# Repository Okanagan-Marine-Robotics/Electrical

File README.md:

# Electrical
Repo For Electrical pcbs and documentation

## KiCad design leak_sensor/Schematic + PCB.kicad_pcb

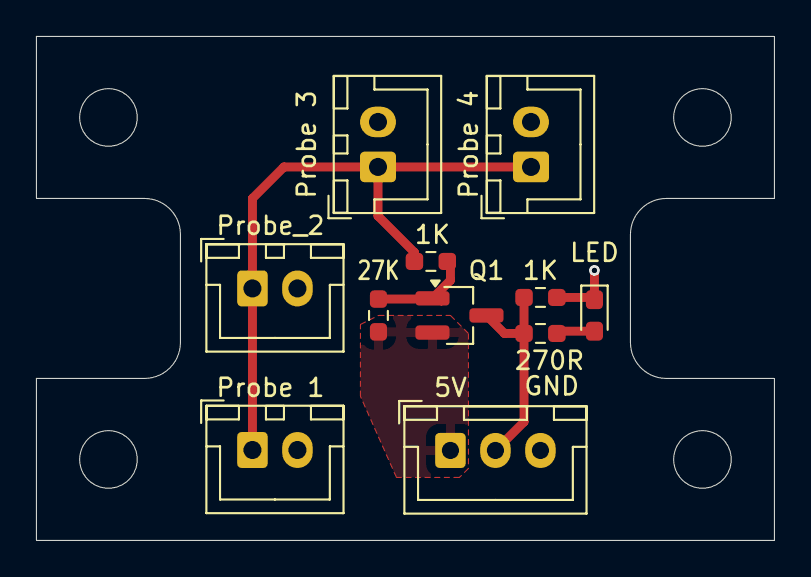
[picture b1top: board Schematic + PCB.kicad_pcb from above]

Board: 2 copper layers, 41.0 x 28.0 mm, 11 parts (0 on the bottom side), 6 nets.

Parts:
J1: 5V; JST_XH_B3B-XH-A_1x03_P2.50mm_Vertical
J2: Probe 3; JST_XH_B2B-XH-A_1x02_P2.50mm_Vertical
J3: Probe 1; JST_XH_B2B-XH-A_1x02_P2.50mm_Vertical
J4: Probe 4; JST_XH_B2B-XH-A_1x02_P2.50mm_Vertical
J5: Probe_2; JST_XH_B2B-XH-A_1x02_P2.50mm_Vertical
LED1: LED; LED_0603_1608Metric_Pad1.05x0.95mm_HandSolder
Q1: BC859W; SOT-23_Handsoldering
R1: 270R; R_0603_1608Metric_Pad0.98x0.95mm_HandSolder
R2, R4: 1K; R_0603_1608Metric_Pad0.98x0.95mm_HandSolder
R3: 27K; R_0603_1608Metric_Pad0.98x0.95mm_HandSolder

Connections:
+5V: J1.1, Q1.2 (E), R3.1
GND: J1.3, J2.2, J3.2, J4.2, J5.2, LED1.1 (K), R2.2
unnamed: J1.2, Q1.3 (C), R1.1, R2.1
unnamed: J2.1, J3.1, J4.1, J5.1, R4.2
unnamed: LED1.2 (A), R1.2
unnamed: Q1.1 (B), R3.2, R4.1

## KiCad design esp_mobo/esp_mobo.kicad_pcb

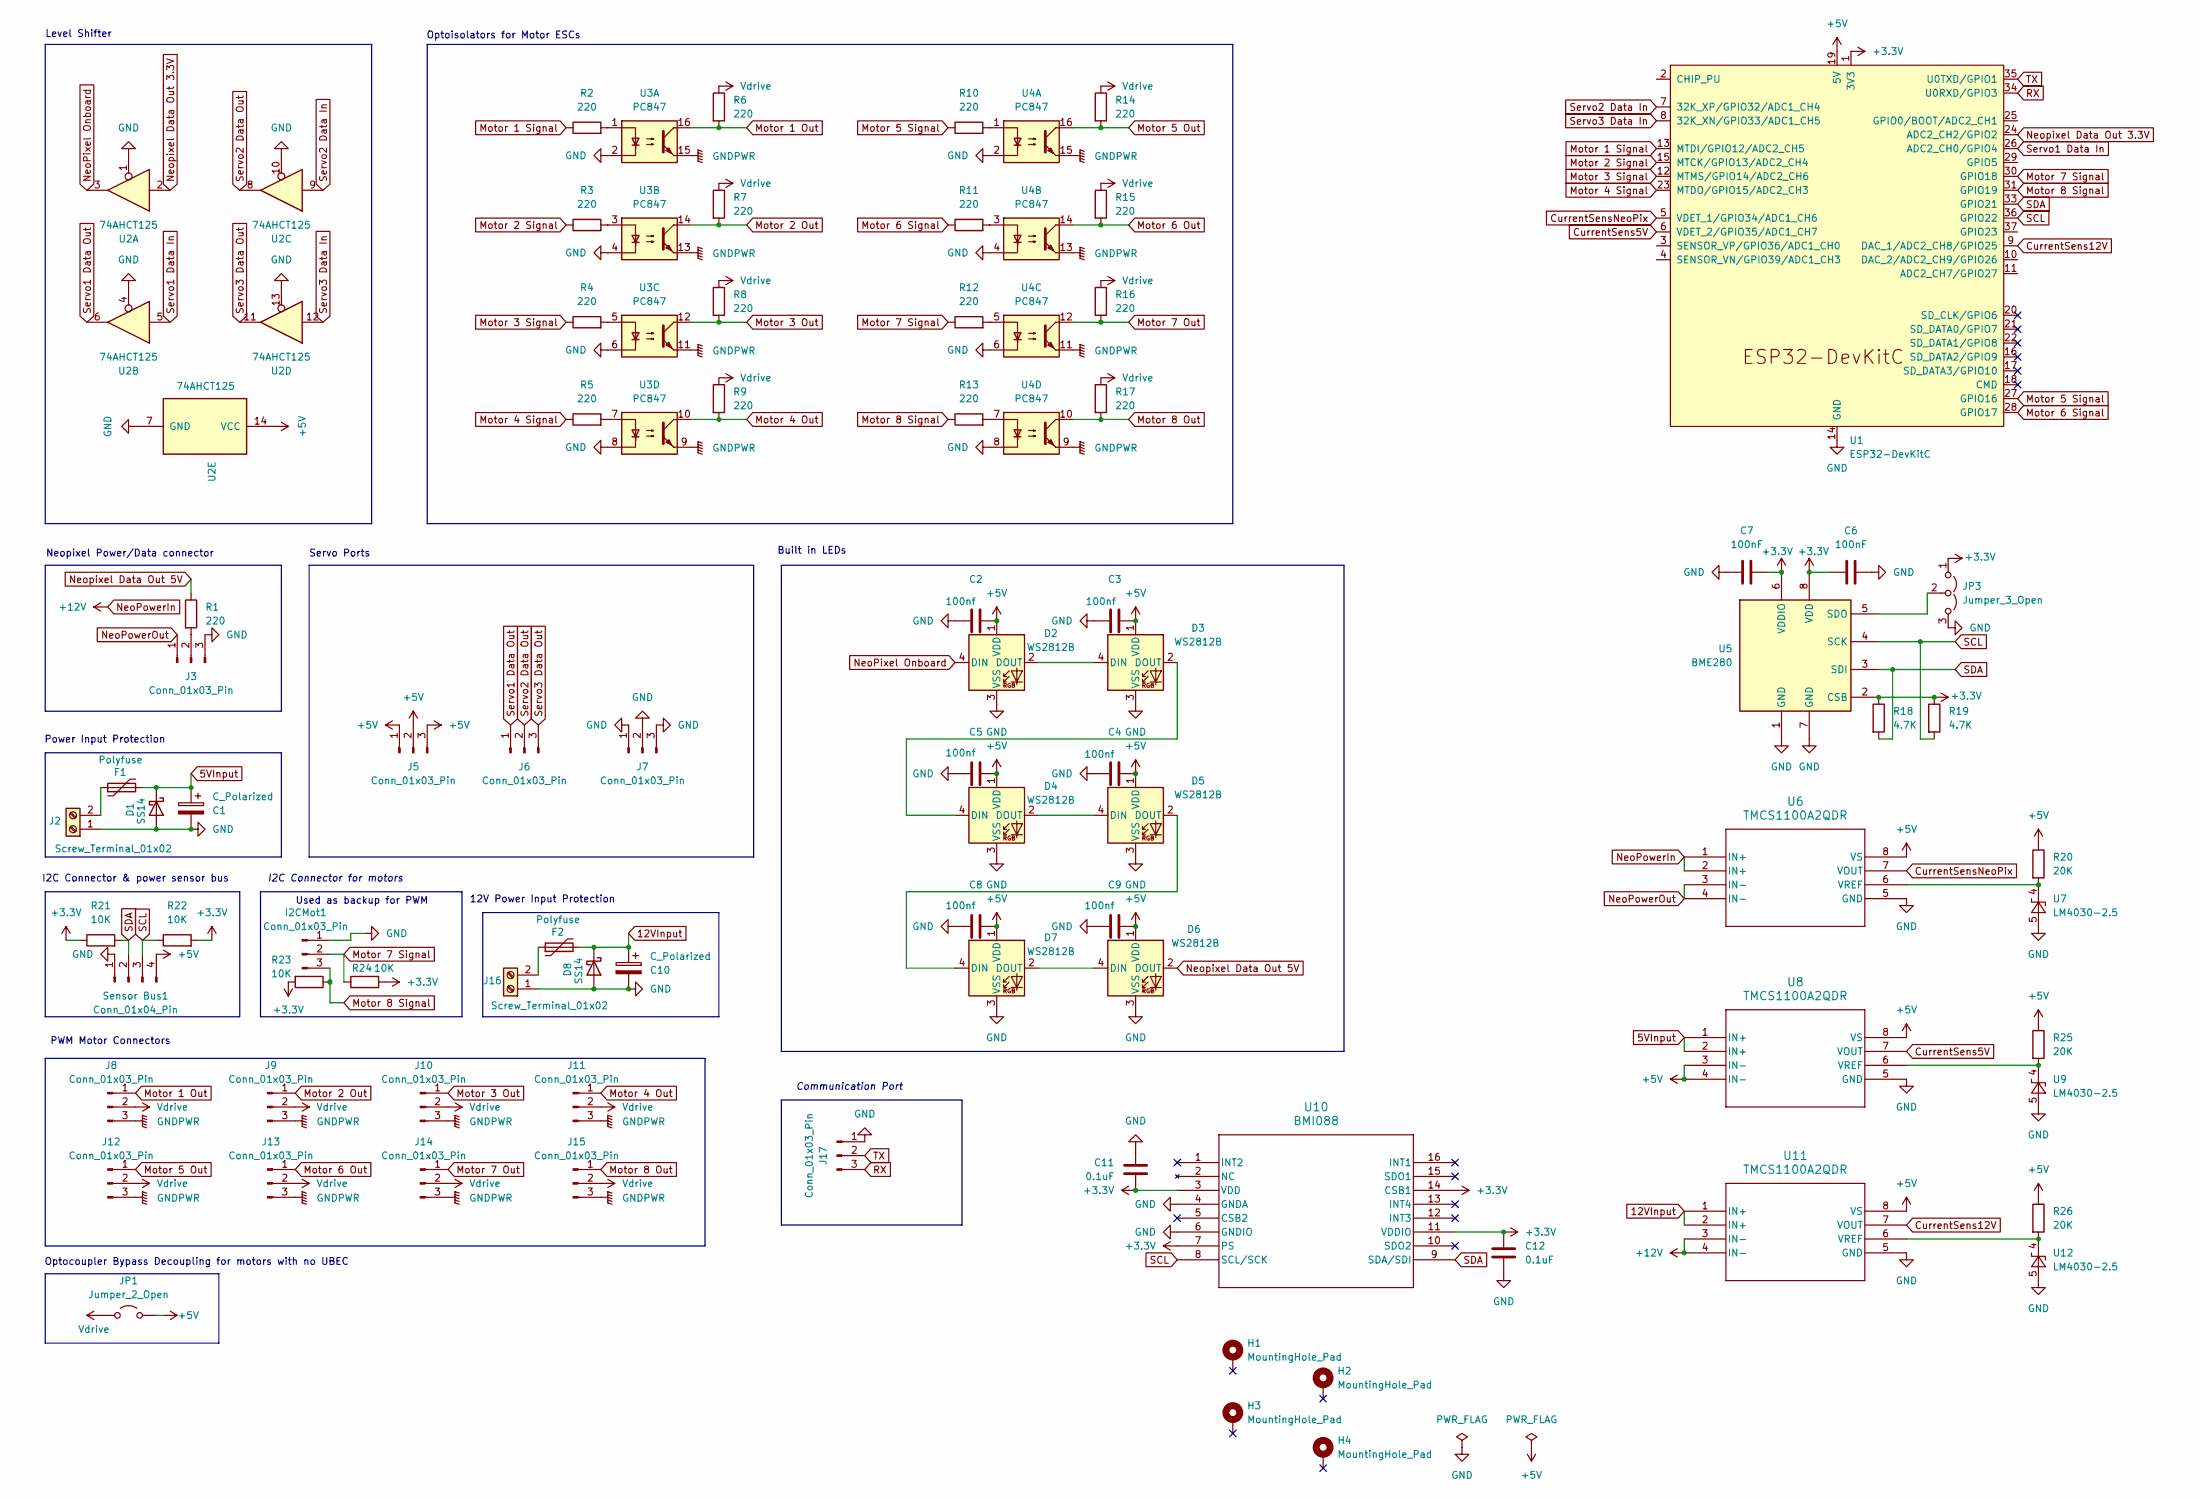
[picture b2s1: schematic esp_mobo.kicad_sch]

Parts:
C1, C10: C_Polarized; CP_Radial_D5.0mm_P2.00mm
C2, C3, C4, C5, C8, C9: 100nf; C_0603_1608Metric
C6, C7: 100nF; C_0603_1608Metric_Pad1.08x0.95mm_HandSolder
C11, C12: 0.1uF; C_0603_1608Metric
D1, D8: SS14; D_SMA
D2, D3, D4, D5, D6, D7: WS2812B; LED_WS2812B_PLCC4_5.0x5.0mm_P3.2mm
F1, F2: Polyfuse; Fuse_Bourns_MF-RG300
H1, H2, H3, H4: MountingHole_Pad; MountingHole_3.2mm_M3_Pad
I2CMot1: Conn_01x03_Pin; JST_XH_B3B-XH-AM_1x03_P2.50mm_Vertical
J2, J16: Screw_Terminal_01x02; TerminalBlock_TE_282834-2_1x02_P2.54mm_Horizontal
J3, J17: Conn_01x03_Pin; JST_XH_B3B-XH-AM_1x03_P2.50mm_Vertical
J5, J6, J7, J8, J9, J10, J11, J12, J13, J14, J15: Conn_01x03_Pin; PinHeader_1x03_P2.54mm_Vertical_small_courtyard
JP1: Jumper_2_Open; PinHeader_1x02_P2.54mm_Vertical
JP3: Jumper_3_Open; PinHeader_1x03_P2.54mm_Vertical
R1: 220; R_0805_2012Metric_Pad1.20x1.40mm_HandSolder
R2, R3, R4, R5, R6, R7, R8, R9, R10, R11, R12, R13, R14, R15, R16, R17: 220; R_0603_1608Metric_Pad0.98x0.95mm_HandSolder
R18, R19: 4.7K; R_0603_1608Metric_Pad0.98x0.95mm_HandSolder
R20, R25, R26: 20K; R_0603_1608Metric_Pad0.98x0.95mm_HandSolder
R21, R22, R23, R24: 10K; R_0603_1608Metric_Pad0.98x0.95mm_HandSolder
Sensor Bus1: Conn_01x04_Pin; JST_XH_B4B-XH-AM_1x04_P2.50mm_Vertical
U1: ESP32-DevKitC
U2: 74AHCT125; DIP-14_W7.62mm
U3, U4: PC847; DIP-16_W7.62mm
U5: BME280; Bosch_LGA-8_2.5x2.5mm_P0.65mm_ClockwisePinNumbering
U6, U8, U11: TMCS1100A2QDR; SOIC8_D_TEX
U7, U9, U12: LM4030-2.5; SOT-23-5
U10: BMI088; QFN_BMI085_BOS

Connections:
5VInput: C1.1, D1.1 (K), F1.2, U8.1 (IN+), U8.2 (IN+)
12VInput: C10.1, D8.1 (K), F2.2, U11.1 (IN+), U11.2 (IN+)
+3.3V: C6.1, C7.2, C11.1, C12.1, JP3.1 (A), R18.1, R19.1, R21.1, R22.2, R23.2, R24.2, U1.1 (3V3), U5.2 (CSB), U5.6 (VDDIO), U5.8 (VDD), U10.3 (VDD), U10.7 (PS), U10.11 (VDDIO), U10.14 (CSB1)
+5V: C2.2, C3.2, C4.2, C5.2, C8.2, C9.2, D2.1 (VDD), D3.1 (VDD), D4.1 (VDD), D5.1 (VDD), D6.1 (VDD), D7.1 (VDD), J5.1, J5.2, J5.3, JP1.2 (B), R20.1, R25.1, R26.1, Sensor Bus1.4, U1.19 (5V), U2.14 (VCC), U6.8 (VS), U8.3 (IN-), U8.4 (IN-), U8.8 (VS), U11.8 (VS)
CurrentSens5V: U1.6 (VDET_2/GPIO35/ADC1_CH7), U8.7 (VOUT)
CurrentSens12V: U1.9 (DAC_1/ADC2_CH8/GPIO25), U11.7 (VOUT)
CurrentSensNeoPix: U1.5 (VDET_1/GPIO34/ADC1_CH6), U6.7 (VOUT)
GND: C1.2, C2.1, C3.1, C4.1, C5.1, C6.2, C7.1, C8.1, C9.1, C10.2, C11.2, C12.2, D1.2 (A), D2.3 (VSS), D3.3 (VSS), D4.3 (VSS), D5.3 (VSS), D6.3 (VSS), D7.3 (VSS), D8.2 (A), I2CMot1.1, J2.1, J3.3, J7.1, J7.2, J7.3, J16.1, J17.1, JP3.3 (B), Sensor Bus1.1, U1.14 (GND), U1.32 (GND), U1.38 (GND), U2.1, U2.4, U2.7 (GND), U2.10, U2.13, U3.2, U3.4, U3.6, U3.8, U4.2, U4.4, U4.6, U4.8, U5.1 (GND), U5.7 (GND), U6.5 (GND), U7.5 (A), U8.5 (GND), U9.5 (A), U10.4 (GNDA), U10.6 (GNDIO), U11.5 (GND), U12.5 (A)
GNDPWR: J8.3, J9.3, J10.3, J11.3, J12.3, J13.3, J14.3, J15.3, U3.9, U3.11, U3.13, U3.15, U4.9, U4.11, U4.13, U4.15
Motor 1 Out: J8.1, R6.2, U3.16
Motor 1 Signal: R2.1, U1.13 (MTDI/GPIO12/ADC2_CH5)
Motor 2 Out: J9.1, R7.2, U3.14
Motor 2 Signal: R3.1, U1.15 (MTCK/GPIO13/ADC2_CH4)
Motor 3 Out: J10.1, R8.2, U3.12
Motor 3 Signal: R4.1, U1.12 (MTMS/GPIO14/ADC2_CH6)
Motor 4 Out: J11.1, R9.2, U3.10
Motor 4 Signal: R5.1, U1.23 (MTDO/GPIO15/ADC2_CH3)
Motor 5 Out: J12.1, R14.2, U4.16
Motor 5 Signal: R10.1, U1.27 (GPIO16)
Motor 6 Out: J13.1, R15.2, U4.14
Motor 6 Signal: R11.1, U1.28 (GPIO17)
Motor 7 Out: J14.1, R16.2, U4.12
Motor 7 Signal: I2CMot1.2, R12.1, R24.1, U1.30 (GPIO18)
Motor 8 Out: J15.1, R17.2, U4.10
Motor 8 Signal: I2CMot1.3, R13.1, R23.1, U1.31 (GPIO19)
NeoPixel Onboard: D2.4 (DIN), U2.3
NeoPowerIn: U6.1 (IN+), U6.2 (IN+), U11.3 (IN-), U11.4 (IN-)
NeoPowerOut: J3.1, U6.3 (IN-), U6.4 (IN-)
Neopixel Data Out 3.3V: U1.24 (ADC2_CH2/GPIO2), U2.2
Neopixel Data Out 5V: D6.2 (DOUT), R1.1
unnamed: D2.2 (DOUT), D3.4 (DIN)
unnamed: D3.2 (DOUT), D4.4 (DIN)
unnamed: D4.2 (DOUT), D5.4 (DIN)
unnamed: D5.2 (DOUT), D7.4 (DIN)
unnamed: D6.4 (DIN), D7.2 (DOUT)
unnamed: F1.1, J2.2
unnamed: J3.2, R1.2
unnamed: F2.1, J16.2
unnamed: JP3.2 (C), U5.5 (SDO)
unnamed: R2.2, U3.1
unnamed: R3.2, U3.3
unnamed: R4.2, U3.5
unnamed: R5.2, U3.7
unnamed: R10.2, U4.1
unnamed: R11.2, U4.3
unnamed: R12.2, U4.5
unnamed: R13.2, U4.7
unnamed: R20.2, U6.6 (VREF), U7.4 (K)
unnamed: R25.2, U8.6 (VREF), U9.4 (K)
unnamed: R26.2, U11.6 (VREF), U12.4 (K)
RX: J17.3, U1.34 (U0RXD/GPIO3)
SCL: R19.2, R22.1, Sensor Bus1.3, U1.36 (GPIO22), U5.4 (SCK), U10.8 (SCL/SCK)
SDA: R18.2, R21.2, Sensor Bus1.2, U1.33 (GPIO21), U5.3 (SDI), U10.9 (SDA/SDI)
Servo1 Data In: U1.26 (ADC2_CH0/GPIO4), U2.5
Servo1 Data Out: J6.1, U2.6
Servo2 Data In: U1.7 (32K_XP/GPIO32/ADC1_CH4), U2.9
Servo2 Data Out: J6.2, U2.8
Servo3 Data In: U1.8 (32K_XN/GPIO33/ADC1_CH5), U2.12
Servo3 Data Out: J6.3, U2.11
TX: J17.2, U1.35 (U0TXD/GPIO1)
Vdrive: J8.2, J9.2, J10.2, J11.2, J12.2, J13.2, J14.2, J15.2, JP1.1 (A), R6.1, R7.1, R8.1, R9.1, R14.1, R15.1, R16.1, R17.1

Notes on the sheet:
Communication Port
Level Shifter
Built in LEDs
12V Power Input Protection
Neopixel Power/Data connector
Servo Ports
PWM Motor Connectors
Used as backup for PWM
I2C Connector for motors
Optocoupler Bypass Decoupling for motors with no UBEC
Optoisolators for Motor ESCs
Power Input Protection
I2C Connector & power sensor bus

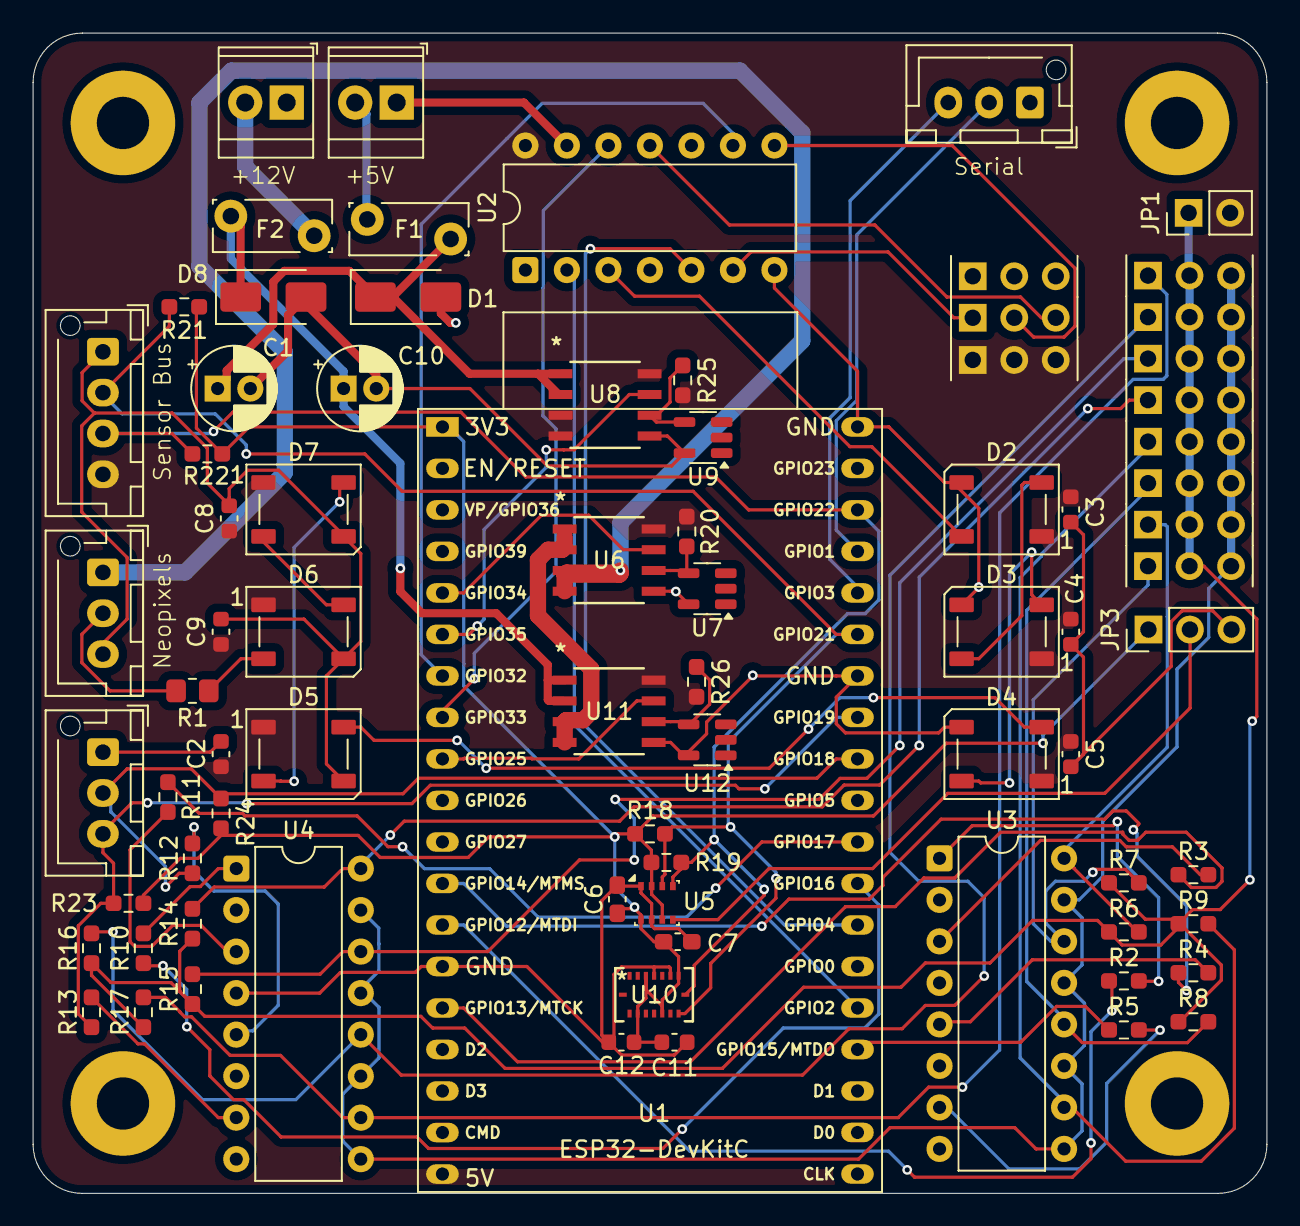
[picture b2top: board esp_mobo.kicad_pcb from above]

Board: 2 copper layers, 75.5 x 71.0 mm, 83 parts (0 on the bottom side), 61 nets.

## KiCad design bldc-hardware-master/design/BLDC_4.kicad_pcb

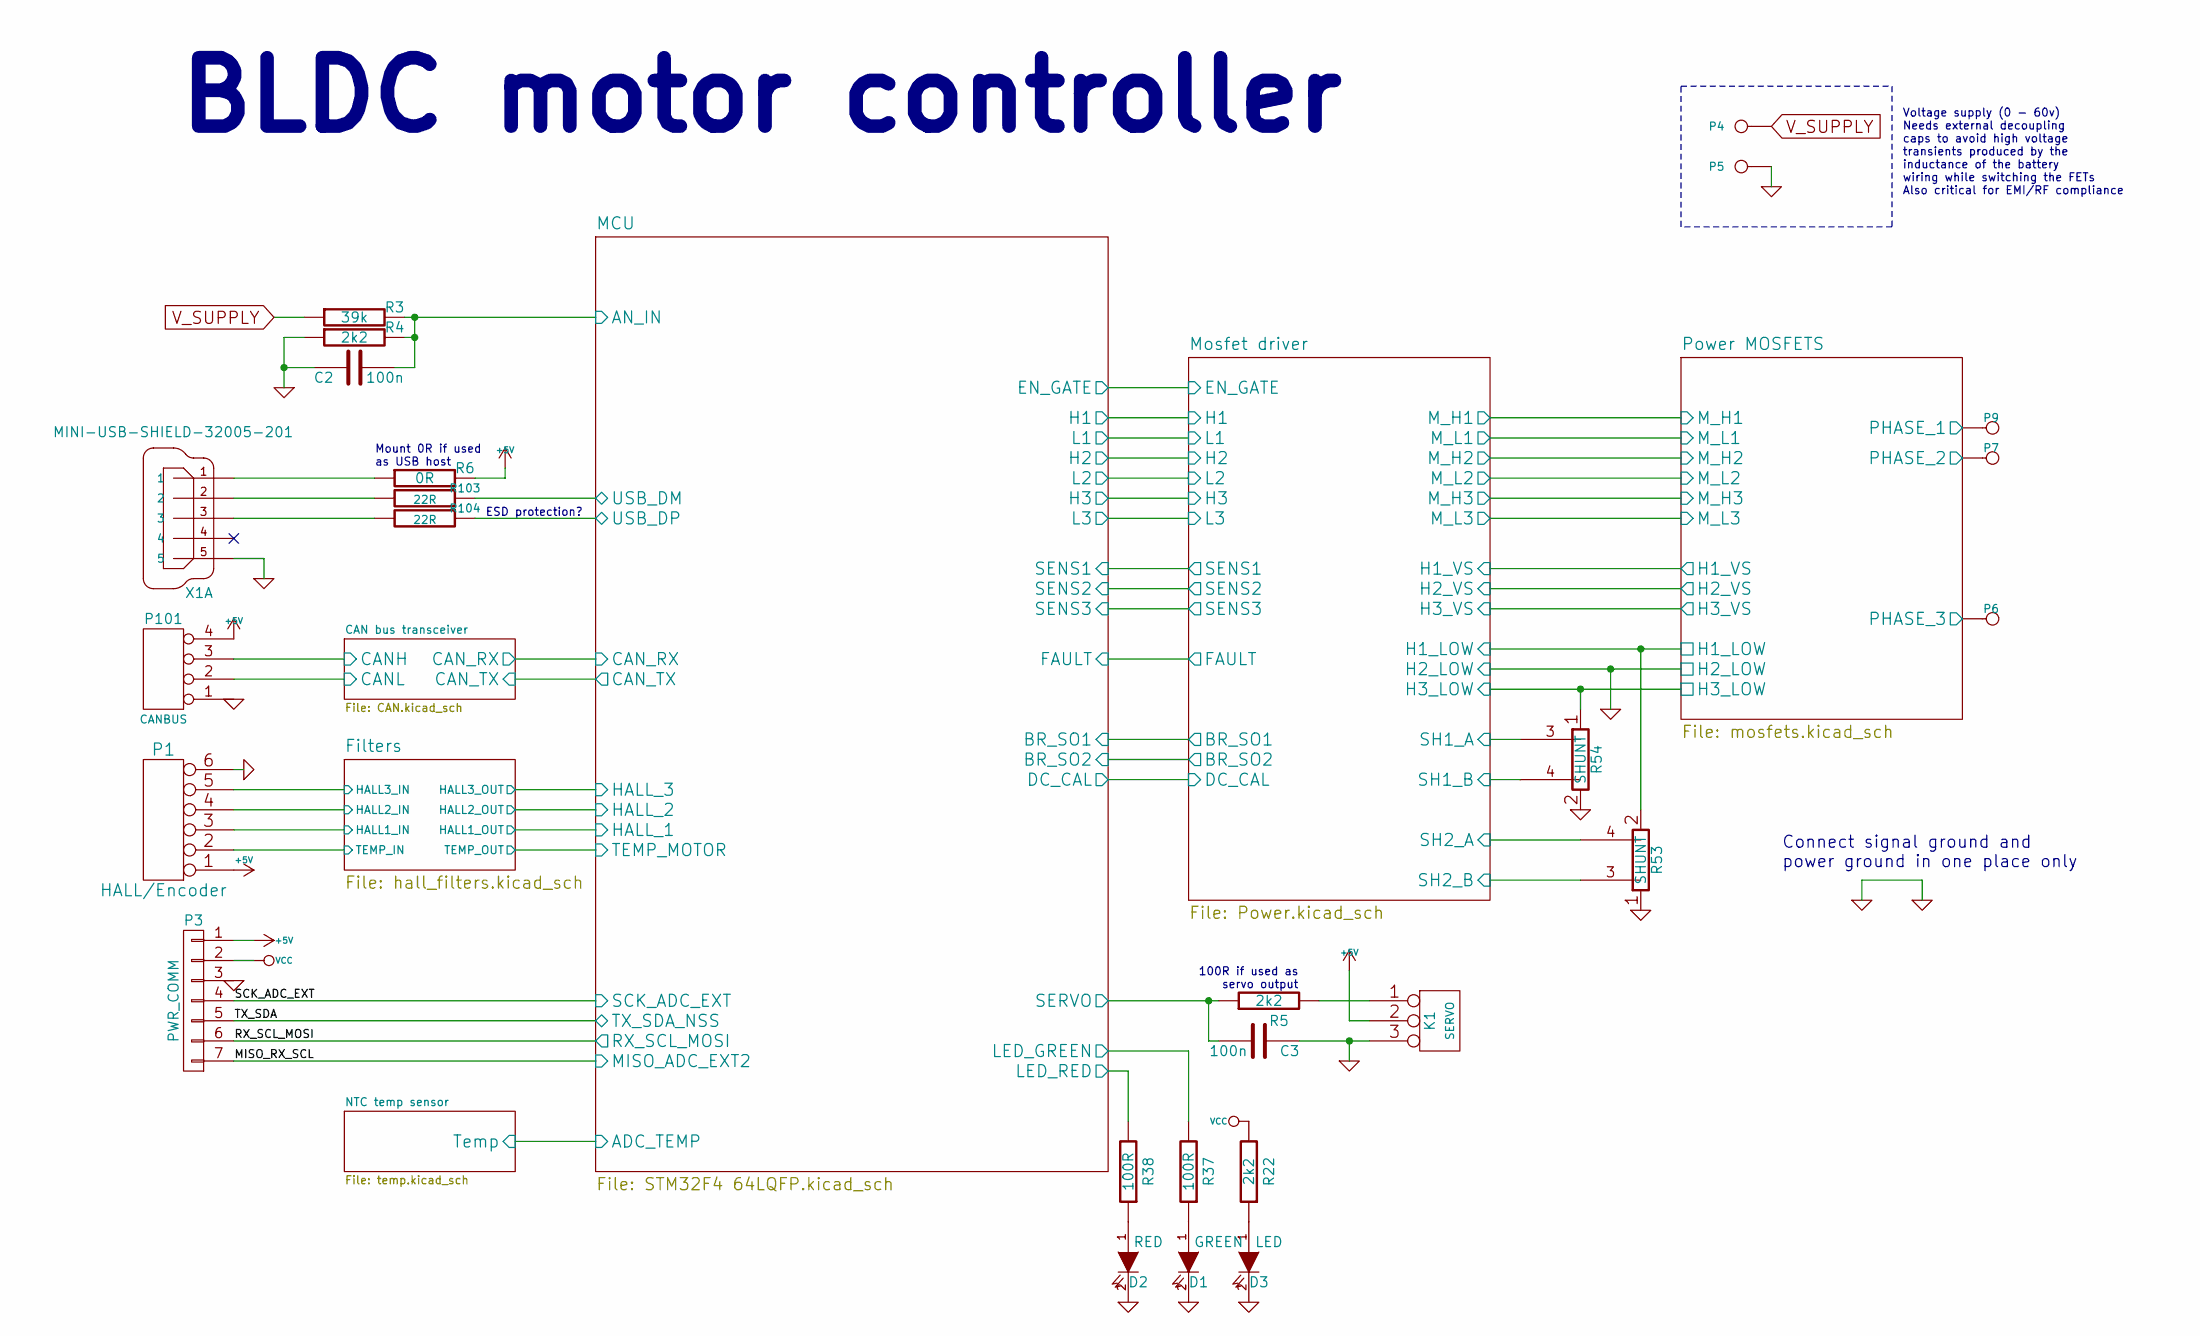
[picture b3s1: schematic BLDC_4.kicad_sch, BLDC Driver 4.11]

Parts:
C2, C3: 100n; SMD-0603_c
D1: GREEN; LED-0603
D2: RED; LED-0603
D3: LED; LED-0603
K1: SERVO; pinhead-1X03
P1: HALL/Encoder; MICRO_JST_6
P3: PWR_COMM; b7b-ph-kl
P4: IN+; 1PAD_4x5mm
P5: IN-; 1PAD_4x5mm
P6: MOTOR1; 1PAD_4x5mm
P7: MOTOR2; 1PAD_4x5mm
P9: MOTOR3; 1PAD_4x5mm
P101: CANBUS; b4b-ph-kl
R3: 39k; SMD-0603_r
R4, R5, R22: 2k2; SMD-0603_r
R6: 0R; SMD-0603_r
R37, R38: 100R; SMD-0603_r
R53, R54: SHUNT; WSLP2726
R103, R104: 22R; SMD-0603_r
X1: MINI-USB-SHIELD-32005-201; USB-UX60R-MB-5ST

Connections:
+5V: K1.2 (PM), P1.1, P3.1, P101.4, R6.2; also elsewhere on the board
/CAN bus transceiver/CANH: P101.3; also elsewhere on the board
/CAN bus transceiver/CANL: P101.2; also elsewhere on the board
/Filters/HALL1_IN: P1.3; also elsewhere on the board
/Filters/HALL2_IN: P1.4; also elsewhere on the board
/Filters/HALL3_IN: P1.5; also elsewhere on the board
/Filters/TEMP_MOTOR: P1.2; also elsewhere on the board
/MCU/AN_IN: C2.2, R3.2, R4.2; also elsewhere on the board
/MCU/LED_GREEN: R37.2; also elsewhere on the board
/MCU/LED_RED: R38.2; also elsewhere on the board
/MCU/SERVO: C3.2, R5.1; also elsewhere on the board
/MCU/USB_DM: R103.1; also elsewhere on the board
/MCU/USB_DP: R104.1; also elsewhere on the board
/MISO_RX_SCL: P3.7; also elsewhere on the board
/Mosfet driver/H1_LOW: R53.2; also elsewhere on the board
/Mosfet driver/H1_VS: P9.1; also elsewhere on the board
/Mosfet driver/H2_VS: P7.1; also elsewhere on the board
/Mosfet driver/H3_LOW: R54.1; also elsewhere on the board
/Mosfet driver/H3_VS: P6.1; also elsewhere on the board
/Mosfet driver/SH1_A: R54.3; also elsewhere on the board
/Mosfet driver/SH1_B: R54.4; also elsewhere on the board
/Mosfet driver/SH2_A: R53.4; also elsewhere on the board
/Mosfet driver/SH2_B: R53.3; also elsewhere on the board
/RX_SCL_MOSI: P3.6; also elsewhere on the board
/SCK_ADC_EXT: P3.4; also elsewhere on the board
/TX_SDA: P3.5; also elsewhere on the board
GND: C2.1, C3.1, D1.2 (K), D2.2 (K), D3.2 (K), K1.3, P1.6, P3.3, P5.1, P101.1, R4.1, R53.1, R54.2, X1.5; also elsewhere on the board
unnamed: D1.1 (A), R37.1
unnamed: D2.1 (A), R38.1
unnamed: D3.1 (A), R22.1
unnamed: K1.1, R5.2
unnamed: R6.1, X1.1
unnamed: R103.2, X1.2
unnamed: R104.2, X1.3
VCC: P3.2, R22.2; also elsewhere on the board
V_SUPPLY: P4.1, R3.1; also elsewhere on the board

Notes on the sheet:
ESD protection?
100R if used as servo output
Connect signal ground and power ground in one place only
BLDC motor controller
Voltage supply (0 - 60v) Needs external decoupling caps to avoid high voltage transients produced by the inductance of the battery wiring while switching the FETs Also critical for EMI/RF compliance
Mount 0R if used as USB host

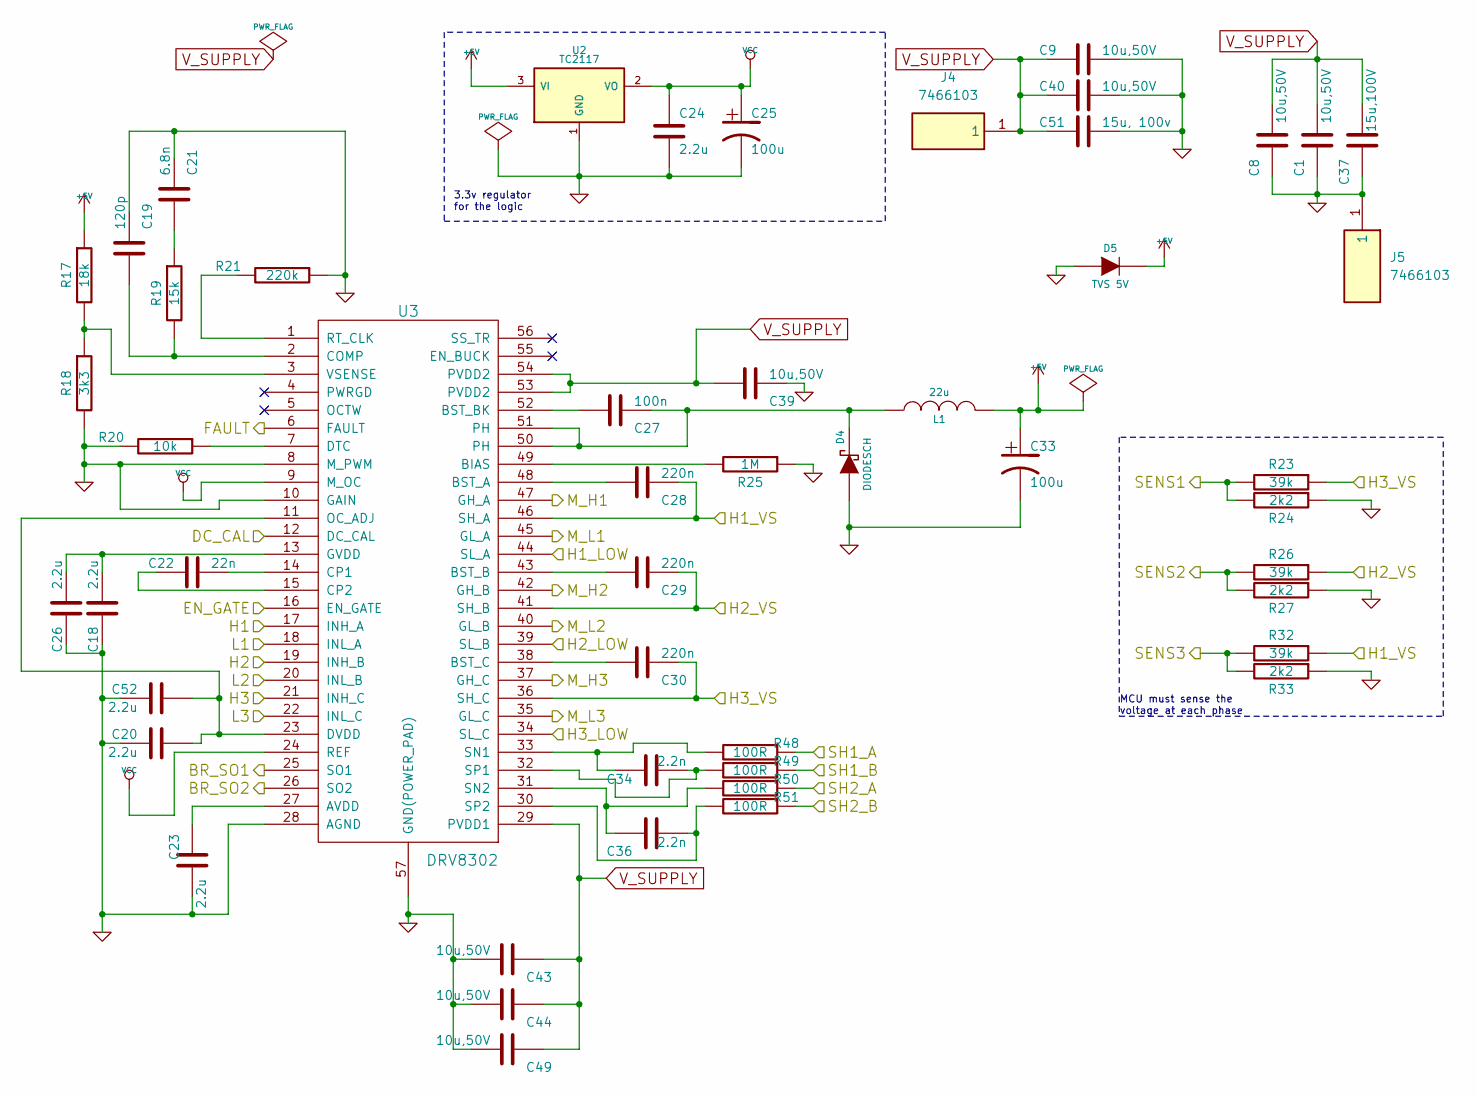
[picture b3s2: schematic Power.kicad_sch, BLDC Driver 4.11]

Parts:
C1, C8, C9, C39, C40, C43, C44, C49: 10u,50V; SMD-1206
C18, C20, C23, C24, C26, C52: 2.2u; SMD-0603_c
C19: 120p; SMD-0603_c
C21: 6.8n; SMD-0603_c
C22: 22n; SMD-0603_c
C25, C33: 100u; c_tant_B
C27: 100n; SMD-0603_c
C28, C29, C30: 220n; SMD-0603_c
C34, C36: 2.2n; SMD-0603_c
C37: 15u,100V; c_2220
C51: 15u, 100v; c_2220
D4: DIODESCH; SMA_Handsoldering
D5: TVS 5V; do214ac
J4, J5: 7466103; Manufacturer_Part_Number 7466103
L1: 22u; inductor_smd_8x5mm
R17: 18k; SMD-0603_r
R18: 3k3; SMD-0603_r
R19: 15k; SMD-0603_r
R20: 10k; SMD-0603_r
R21: 220k; SMD-0603_r
R23, R26, R32: 39k; SMD-0603_r
R24, R27, R33: 2k2; SMD-0603_r
R25: 1M; SMD-0603_r
R48, R49, R50, R51: 100R; SMD-0603_r
U2: TC2117; SOT-223
U3: DRV8302; TSSOP-56-PP

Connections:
+5V: C33.1, D5.2 (K), L1.2, R17.1, U2.3 (VI); also elsewhere on the board
/MCU/BR_SO1: U3.25 (SO1); also elsewhere on the board
/MCU/BR_SO2: U3.26 (SO2); also elsewhere on the board
/MCU/DC_CAL: U3.12 (DC_CAL); also elsewhere on the board
/MCU/EN_GATE: U3.16 (EN_GATE); also elsewhere on the board
/MCU/FAULT: U3.6 (FAULT); also elsewhere on the board
/MCU/H1: U3.17 (INH_A); also elsewhere on the board
/MCU/H2: U3.19 (INH_B); also elsewhere on the board
/MCU/H3: U3.21 (INH_C); also elsewhere on the board
/MCU/L1: U3.18 (INL_A); also elsewhere on the board
/MCU/L2: U3.20 (INL_B); also elsewhere on the board
/MCU/L3: U3.22 (INL_C); also elsewhere on the board
/MCU/SENS1: R23.2, R24.2; also elsewhere on the board
/MCU/SENS2: R26.2, R27.2; also elsewhere on the board
/MCU/SENS3: R32.2, R33.2; also elsewhere on the board
/Mosfet driver/H1_LOW: U3.44 (SL_A); also elsewhere on the board
/Mosfet driver/H1_VS: C28.1, R32.1, U3.46 (SH_A); also elsewhere on the board
/Mosfet driver/H2_VS: C29.1, R26.1, U3.41 (SH_B); also elsewhere on the board
/Mosfet driver/H3_LOW: U3.34 (SL_C); also elsewhere on the board
/Mosfet driver/H3_VS: C30.1, R23.1, U3.36 (SH_C); also elsewhere on the board
/Mosfet driver/M_H1: U3.47 (GH_A); also elsewhere on the board
/Mosfet driver/M_H2: U3.42 (GH_B); also elsewhere on the board
/Mosfet driver/M_H3: U3.37 (GH_C); also elsewhere on the board
/Mosfet driver/M_L1: U3.45 (GL_A); also elsewhere on the board
/Mosfet driver/M_L2: U3.40 (GL_B); also elsewhere on the board
/Mosfet driver/M_L3: U3.35 (GL_C); also elsewhere on the board
/Mosfet driver/SH1_A: R48.1; also elsewhere on the board
/Mosfet driver/SH1_B: R49.1; also elsewhere on the board
/Mosfet driver/SH2_A: R50.1; also elsewhere on the board
/Mosfet driver/SH2_B: R51.1; also elsewhere on the board
GND: C1.1, C8.1, C9.1, C18.2, C19.1, C20.1, C21.1, C23.1, C24.2, C25.2, C26.2, C33.2, C37.1, C39.1, C40.1, C43.2, C44.2, C49.2, C51.1, C52.1, D4.1 (A), D5.1 (A), J5.1, R18.2, R20.2, R21.1, R24.1, R25.1, R27.1, R33.1, U2.1 (GND), U3.8 (M_PWM), U3.10 (GAIN), U3.28 (AGND), U3.39 (SL_B), U3.57 (GND(POWER_PAD)); also elsewhere on the board
unnamed: C21.2, R19.1
unnamed: C27.1, D4.2 (K), L1.1, U3.50 (PH), U3.51 (PH)
unnamed: C23.2, U3.27 (AVDD)
unnamed: R25.2, U3.49 (BIAS)
unnamed: C28.2, U3.48 (BST_A)
unnamed: C29.2, U3.43 (BST_B)
unnamed: C27.2, U3.52 (BST_BK)
unnamed: C30.2, U3.38 (BST_C)
unnamed: C19.2, R19.2, U3.2 (COMP)
unnamed: C22.1, U3.14 (CP1)
unnamed: C22.2, U3.15 (CP2)
unnamed: R20.1, U3.7 (DTC)
unnamed: C20.2, C52.2, U3.11 (OC_ADJ), U3.23 (DVDD)
unnamed: C18.1, C26.1, U3.13 (GVDD)
unnamed: R21.2, U3.1 (RT_CLK)
unnamed: C34.1, R48.2, U3.33 (SN1)
unnamed: C36.1, R50.2, U3.31 (SN2)
unnamed: C34.2, R49.2, U3.32 (SP1)
unnamed: C36.2, R51.2, U3.30 (SP2)
unnamed: R17.2, R18.1, U3.3 (VSENSE)
VCC: C24.1, C25.1, U2.2 (VO), U3.9 (M_OC), U3.24 (REF); also elsewhere on the board
V_SUPPLY: C1.2, C8.2, C9.2, C37.2, C39.2, C40.2, C43.1, C44.1, C49.1, C51.2, J4.1, U3.29 (PVDD1), U3.53 (PVDD2), U3.54 (PVDD2); also elsewhere on the board

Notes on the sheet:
3.3v regulator for the logic
MCU must sense the voltage at each phase

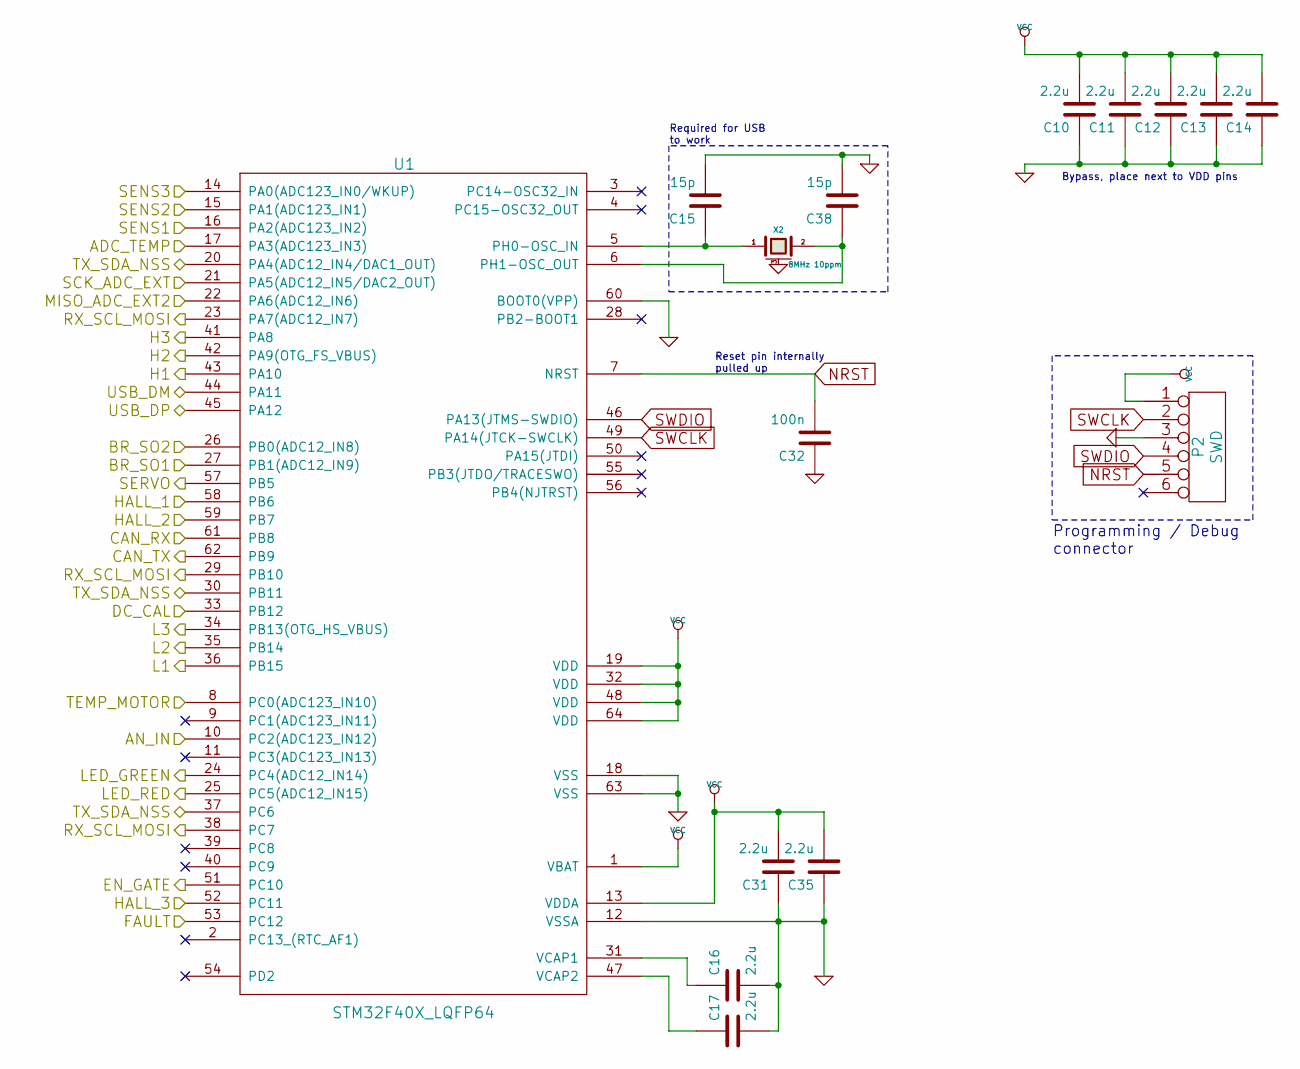
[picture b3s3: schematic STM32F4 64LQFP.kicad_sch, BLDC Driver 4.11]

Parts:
C10, C11, C12, C13, C14, C16, C17, C31, C35: 2.2u; SMD-0603_c
C15, C38: 15p; SMD-0603_c
C32: 100n; SMD-0603_c
P2: SWD; MICRO_JST_6
U1: STM32F40X_LQFP64; lqfp64_pad_mod
X2: 8MHz 10ppm; Crystal_5x3mm; mfg# ABM3B-8.0-10-1UT

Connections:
/CAN bus transceiver/CAN_RX: U1.61 (PB8); also elsewhere on the board
/CAN bus transceiver/CAN_TX: U1.62 (PB9); also elsewhere on the board
/Filters/HALL1_OUT: U1.58 (PB6); also elsewhere on the board
/Filters/HALL2_OUT: U1.59 (PB7); also elsewhere on the board
/Filters/HALL3_OUT: U1.52 (PC11); also elsewhere on the board
/Filters/TEMP_MOTOR: U1.8 (PC0(ADC123_IN10)); also elsewhere on the board
/MCU/ADC_TEMP: U1.17 (PA3(ADC123_IN3)); also elsewhere on the board
/MCU/AN_IN: U1.10 (PC2(ADC123_IN12)); also elsewhere on the board
/MCU/BR_SO1: U1.27 (PB1(ADC12_IN9)); also elsewhere on the board
/MCU/BR_SO2: U1.26 (PB0(ADC12_IN8)); also elsewhere on the board
/MCU/DC_CAL: U1.33 (PB12); also elsewhere on the board
/MCU/EN_GATE: U1.51 (PC10); also elsewhere on the board
/MCU/FAULT: U1.53 (PC12); also elsewhere on the board
/MCU/H1: U1.43 (PA10); also elsewhere on the board
/MCU/H2: U1.42 (PA9(OTG_FS_VBUS)); also elsewhere on the board
/MCU/H3: U1.41 (PA8); also elsewhere on the board
/MCU/L1: U1.36 (PB15); also elsewhere on the board
/MCU/L2: U1.35 (PB14); also elsewhere on the board
/MCU/L3: U1.34 (PB13(OTG_HS_VBUS)); also elsewhere on the board
/MCU/LED_GREEN: U1.24 (PC4(ADC12_IN14)); also elsewhere on the board
/MCU/LED_RED: U1.25 (PC5(ADC12_IN15)); also elsewhere on the board
/MCU/SENS1: U1.16 (PA2(ADC123_IN2)); also elsewhere on the board
/MCU/SENS2: U1.15 (PA1(ADC123_IN1)); also elsewhere on the board
/MCU/SENS3: U1.14 (PA0(ADC123_IN0/WKUP)); also elsewhere on the board
/MCU/SERVO: U1.57 (PB5); also elsewhere on the board
/MCU/USB_DM: U1.44 (PA11); also elsewhere on the board
/MCU/USB_DP: U1.45 (PA12); also elsewhere on the board
/MISO_RX_SCL: U1.22 (PA6(ADC12_IN6)); also elsewhere on the board
/RX_SCL_MOSI: U1.23 (PA7(ADC12_IN7)), U1.29 (PB10), U1.38 (PC7); also elsewhere on the board
/SCK_ADC_EXT: U1.21 (PA5(ADC12_IN5/DAC2_OUT)); also elsewhere on the board
/TX_SDA: U1.20 (PA4(ADC12_IN4/DAC1_OUT)), U1.30 (PB11), U1.37 (PC6); also elsewhere on the board
GND: C10.1, C11.1, C12.1, C13.1, C14.1, C15.2, C16.2, C17.2, C31.1, C32.1, C35.1, C38.2, P2.3, U1.12 (VSSA), U1.18 (VSS), U1.60 (BOOT0(VPP)), U1.63 (VSS), X2.3 (case); also elsewhere on the board
NRST: C32.2, P2.5, U1.7 (NRST)
unnamed: C15.1, U1.5 (PH0-OSC_IN), X2.1
unnamed: C38.1, U1.6 (PH1-OSC_OUT), X2.2
unnamed: C16.1, U1.31 (VCAP1)
unnamed: C17.1, U1.47 (VCAP2)
SWCLK: P2.2, U1.49 (PA14(JTCK-SWCLK))
SWDIO: P2.4, U1.46 (PA13(JTMS-SWDIO))
VCC: C10.2, C11.2, C12.2, C13.2, C14.2, C31.2, C35.2, P2.1, U1.1 (VBAT), U1.13 (VDDA), U1.19 (VDD), U1.32 (VDD), U1.48 (VDD), U1.64 (VDD); also elsewhere on the board

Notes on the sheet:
Bypass, place next to VDD pins
Reset pin internally pulled up
Required for USB to work
Programming / Debug connector

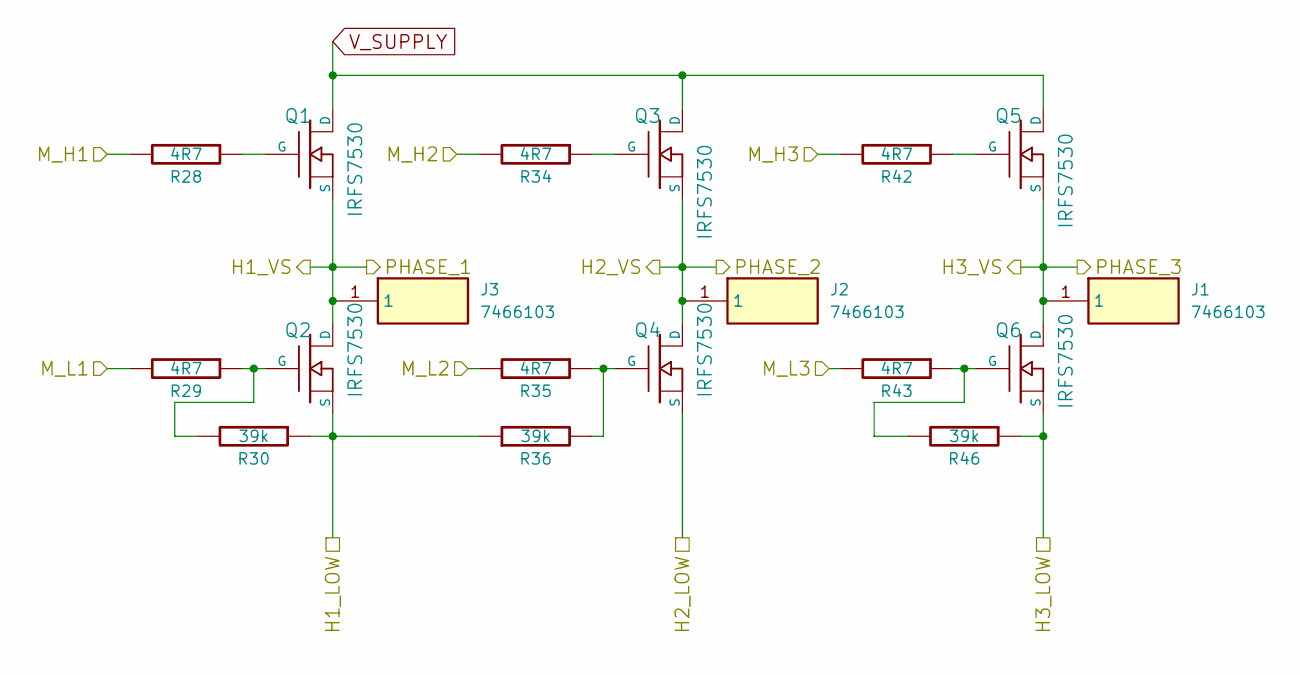
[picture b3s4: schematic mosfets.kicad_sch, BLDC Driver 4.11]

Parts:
J1, J2, J3: 7466103; Manufacturer_Part_Number 7466103
Q1, Q2, Q3, Q4, Q5, Q6: IRFS7530; D2PAK-7-GDS
R28, R29, R34, R35, R42, R43: 4R7; SMD-0603_r
R30, R36, R46: 39k; SMD-0603_r

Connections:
/Mosfet driver/H1_LOW: Q2.S, R30.1, R36.1; also elsewhere on the board
/Mosfet driver/H1_VS: J3.1, Q1.S, Q2.D; also elsewhere on the board
/Mosfet driver/H2_VS: J2.1, Q3.S, Q4.D; also elsewhere on the board
/Mosfet driver/H3_LOW: Q6.S, R46.1; also elsewhere on the board
/Mosfet driver/H3_VS: J1.1, Q5.S, Q6.D; also elsewhere on the board
/Mosfet driver/M_H1: R28.2; also elsewhere on the board
/Mosfet driver/M_H2: R34.2; also elsewhere on the board
/Mosfet driver/M_H3: R42.2; also elsewhere on the board
/Mosfet driver/M_L1: R29.2; also elsewhere on the board
/Mosfet driver/M_L2: R35.2; also elsewhere on the board
/Mosfet driver/M_L3: R43.2; also elsewhere on the board
GND: Q4.S; also elsewhere on the board
unnamed: Q1.G, R28.1
unnamed: Q2.G, R29.1, R30.2
unnamed: Q3.G, R34.1
unnamed: Q4.G, R35.1, R36.2
unnamed: Q5.G, R42.1
unnamed: Q6.G, R43.1, R46.2
V_SUPPLY: Q1.D, Q3.D, Q5.D; also elsewhere on the board
